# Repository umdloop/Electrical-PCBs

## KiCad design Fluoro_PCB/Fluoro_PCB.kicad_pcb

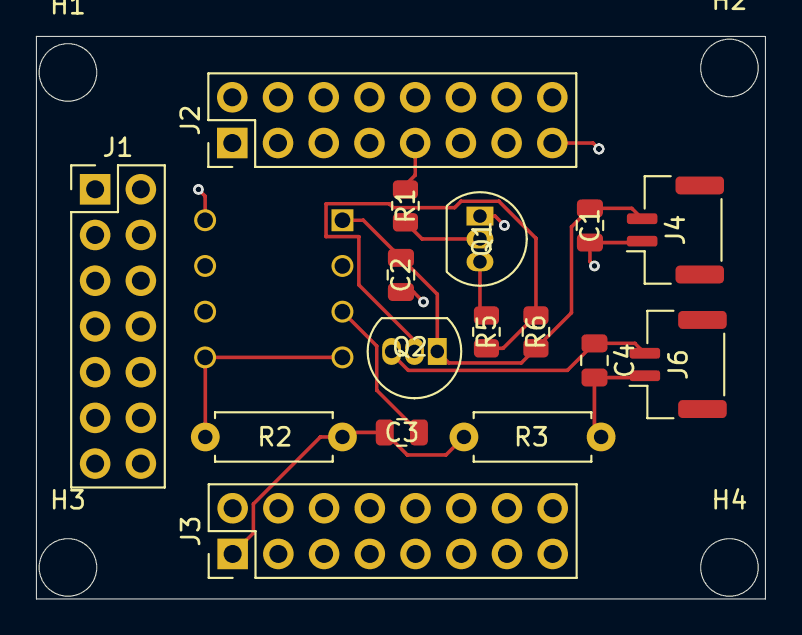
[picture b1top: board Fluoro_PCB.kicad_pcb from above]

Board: 2 copper layers, 40.5 x 31.2 mm, 21 parts (1 on the bottom side), 9 nets.

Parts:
C1, C4: 10uF; C_0805_2012Metric
C2: 100nF; C_0805_2012Metric
C3: 22uF; C_0805_2012Metric
H1, H2, H3, H4: MountingHole; MountingHole_3.2mm_M3_DIN965
J1: Conn_02x07_Odd_Even; PinHeader_2x07_P2.54mm_Vertical
J2, J3: Conn_02x08_Odd_Even; PinHeader_2x08_P2.54mm_Vertical
J4, J6: SM02B-GHS-TB; JST_GH_SM02B-GHS-TB_1x02-1MP_P1.25mm_Horizontal
Q1: S8050; TO-92_Inline
Q2: S8550; TO-92_Inline
R1: 220; R_0805_2012Metric
R2: 18000; R_Axial_DIN0207_L6.3mm_D2.5mm_P7.62mm_Horizontal
R3: 22000; R_Axial_DIN0207_L6.3mm_D2.5mm_P7.62mm_Horizontal
R5: 680; R_0805_2012Metric
R6: 330; R_0805_2012Metric
U1: OPT101P; DIP762W46P254L952H419Q8

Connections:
+5V: C1.1, C2.1, J4.2, Q2.1 (E), R6.1, U1.1 (VS)
/43: C3.1, J3.1, R2.2, R3.2
/54: J2.9, R1.2
GND: C1.2, C2.2, C3.2, C4.2, J2.15, J4.1, J6.1, Q1.1 (E), R3.1, U1.3 (-V), U1.8 (COMMON)
unnamed: Q1.2 (B), R1.1
unnamed: Q1.3 (C), R5.2
unnamed: Q2.2 (B), R5.1, R6.2
unnamed: C4.1, J6.2, Q2.3 (C)
unnamed: R2.1, U1.4 (1MOHM_FB), U1.5 (OUTPUT)

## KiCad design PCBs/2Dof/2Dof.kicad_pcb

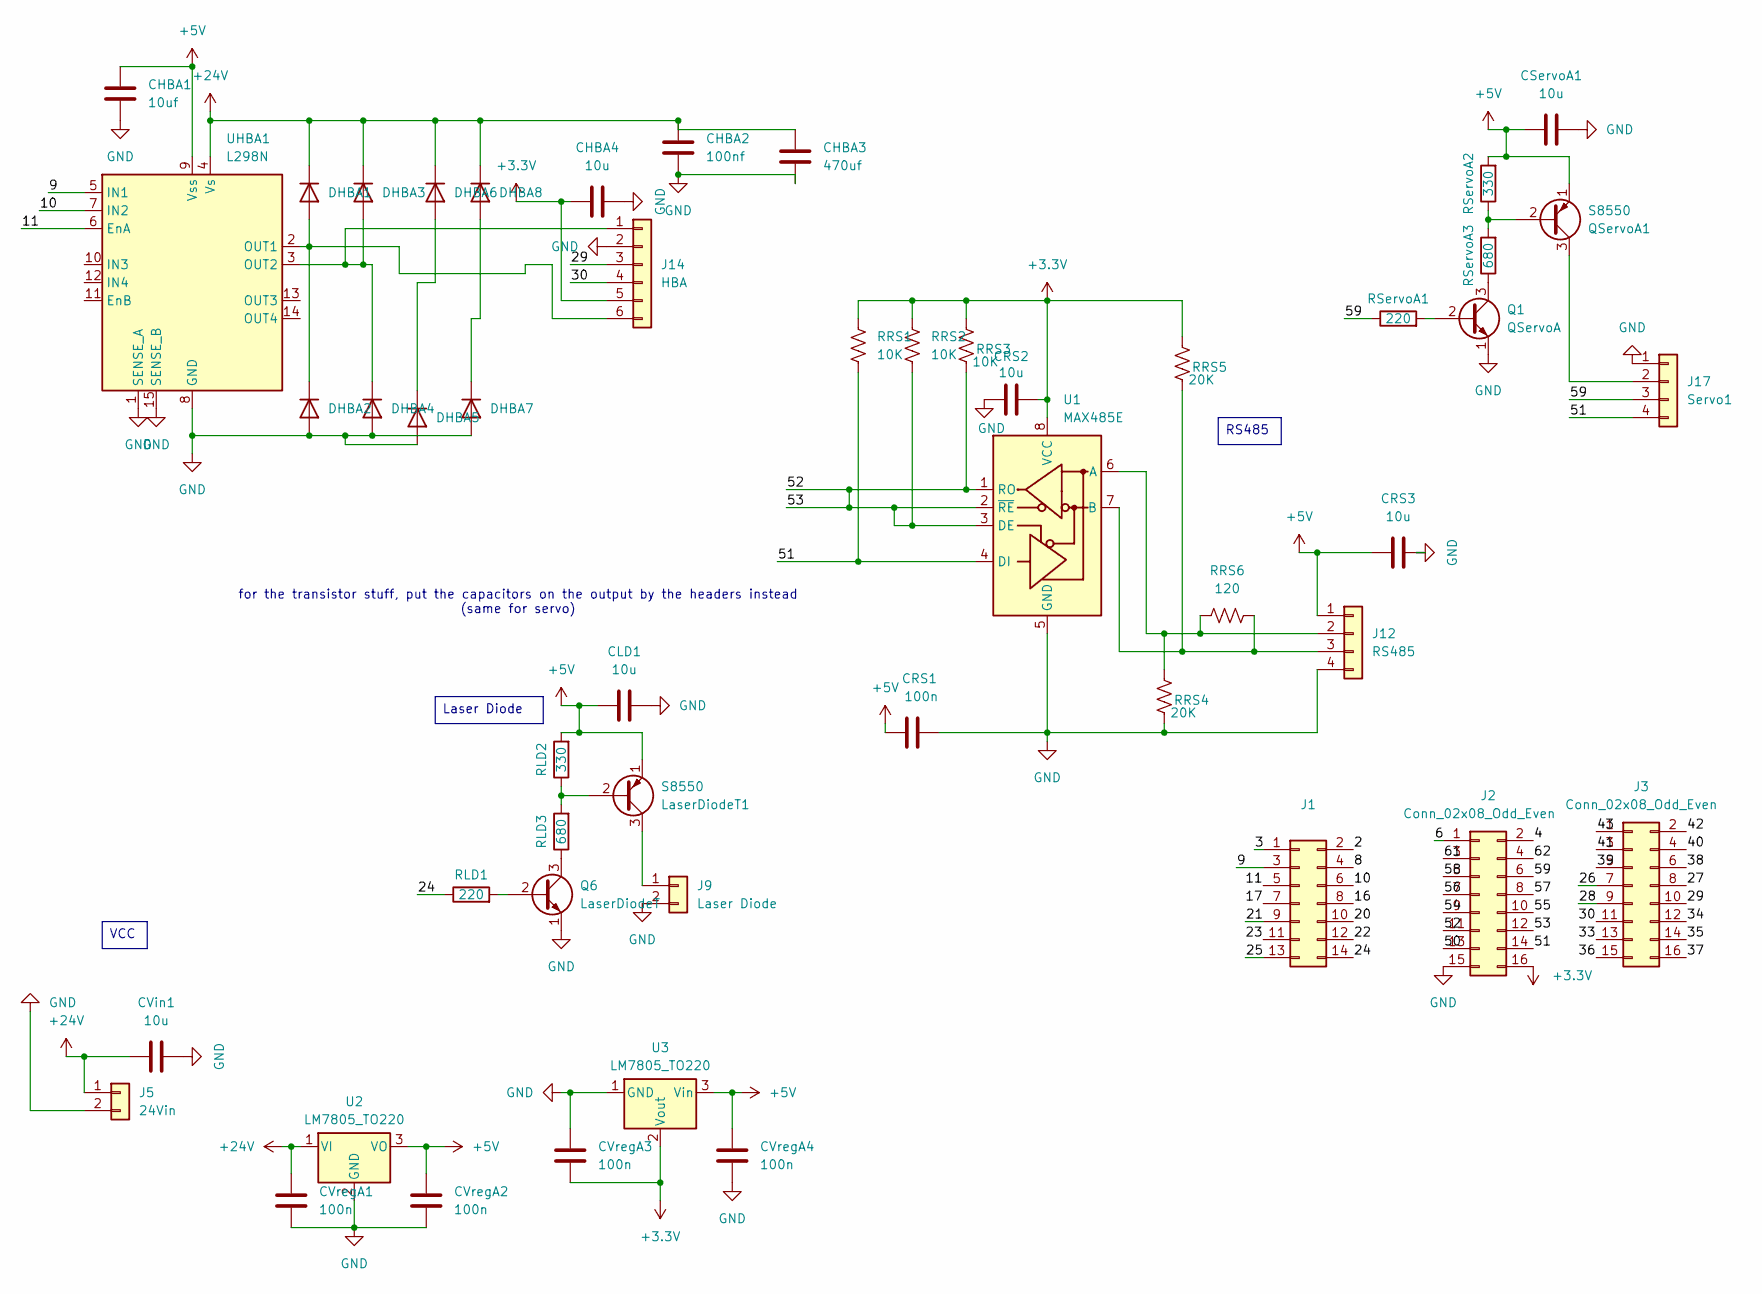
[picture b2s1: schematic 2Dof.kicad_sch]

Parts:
CHBA1: 10uf; C_0805_2012Metric_Pad1.18x1.45mm_HandSolder
CHBA2: 100nf; C_0805_2012Metric_Pad1.18x1.45mm_HandSolder
CHBA3: 470uf; CP_Elec_6.3x7.7
CHBA4: 10u; C_0805_2012Metric_Pad1.18x1.45mm_HandSolder
CLD1: 10u; C_0805_2012Metric_Pad1.18x1.45mm_HandSolder
CRS1: 100n; C_0805_2012Metric_Pad1.18x1.45mm_HandSolder
CRS2, CRS3: 10u; C_0805_2012Metric_Pad1.18x1.45mm_HandSolder
CServoA1: 10u; C_0805_2012Metric_Pad1.18x1.45mm_HandSolder
CVin1: 10u; C_0805_2012Metric_Pad1.18x1.45mm_HandSolder
CVregA1, CVregA2, CVregA3, CVregA4: 100n; C_0805_2012Metric_Pad1.18x1.45mm_HandSolder
DHBA1, DHBA2, DHBA3, DHBA4, DHBA5, DHBA6, DHBA7, DHBA8: 1N4148WT; D_SOD-123
J1: Conn_02x07_Odd_Even; PinHeader_2x07_P2.54mm_Vertical
J2, J3: Conn_02x08_Odd_Even; PinHeader_2x08_P2.54mm_Vertical
J5: 24Vin; Molex_Micro-Fit_3.0_43650-0210_1x02-1MP_P3.00mm_Horizontal
J9: Laser Diode; JST_GH_SM02B-GHS-TB_1x02-1MP_P1.25mm_Horizontal
J12: RS485; JST_GH_SM04B-GHS-TB_1x04-1MP_P1.25mm_Horizontal
J14: HBA; JST_GH_SM06B-GHS-TB_1x06-1MP_P1.25mm_Horizontal
J17: Servo1; JST_GH_SM04B-GHS-TB_1x04-1MP_P1.25mm_Horizontal
LaserDiodeT1: S8550; TO-92_Inline
Q1: QServoA; TO-92_Inline
Q6: LaserDiodeT; TO-92_Inline
QServoA1: S8550; TO-92_Inline
RLD1: 220; R_0402_1005Metric_Pad0.72x0.64mm_HandSolder
RLD2: 330; R_0402_1005Metric_Pad0.72x0.64mm_HandSolder
RLD3: 680; R_0402_1005Metric_Pad0.72x0.64mm_HandSolder
RRS1, RRS2, RRS3: 10K; R_0402_1005Metric_Pad0.72x0.64mm_HandSolder
RRS4, RRS5: 20K; R_0402_1005Metric_Pad0.72x0.64mm_HandSolder
RRS6: 120; R_0402_1005Metric_Pad0.72x0.64mm_HandSolder
RServoA1: 220; R_0402_1005Metric_Pad0.72x0.64mm_HandSolder
RServoA2: 330; R_0402_1005Metric_Pad0.72x0.64mm_HandSolder
RServoA3: 680; R_0402_1005Metric_Pad0.72x0.64mm_HandSolder
U1: MAX485E; SOIC-8_3.9x4.9mm_P1.27mm
U2: LM7805_TO220; TO-220-3_Vertical
U3: LM7805_TO220; SOT-23_Handsoldering
UHBA1: L298N; l298n_with_heatsink

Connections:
+3.3V: CHBA4.1, CRS2.2, CVregA3.1, J2.16, J14.5, RRS1.1, RRS2.1, RRS3.1, RRS5.1, U1.8 (VCC), U3.2 (Vout)
+5V: CHBA1.1, CLD1.2, CRS1.2, CRS3.1, CServoA1.2, CVregA2.2, CVregA4.1, J12.1, LaserDiodeT1.1 (E), QServoA1.1 (E), RLD2.2, RServoA2.2, U2.3 (VO), U3.3 (Vin), UHBA1.9 (Vss)
+24V: CHBA2.1, CHBA3.1, CVin1.1, CVregA1.2, DHBA1.1 (K), DHBA3.1 (K), DHBA6.1 (K), DHBA8.1 (K), J5.1, U2.1 (VI), UHBA1.4 (Vs)
/2: J1.2
/3: J1.1
/4: J2.2
/6: J2.1
/8: J1.4
/9: J1.3, UHBA1.5 (IN1)
/10: J1.6, UHBA1.7 (IN2)
/11: J1.5, UHBA1.6 (EnA)
/16: J1.8
/17: J1.7
/20: J1.10
/21: J1.9
/22: J1.12
/23: J1.11
/24: J1.14, RLD1.1
/25: J1.13
/26: J3.7
/27: J3.8
/28: J3.9
/29: J3.10, J14.3
/30: J3.11, J14.4
/33: J3.13
/34: J3.12
/35: J3.14
/36: J3.15
/37: J3.16
/38: J3.6
/39: J3.5
/40: J3.4
/41: J3.3
/42: J3.2
/43: J3.1
/50: J2.13
/51: J2.14, J17.4, RRS1.2, U1.4 (DI)
/52: J2.11, J2.12, RRS2.2, RRS3.2, U1.1 (RO), U1.2 (~RE), U1.3 (DE)
/54: J2.9
/55: J2.10
/56: J2.7
/57: J2.8
/58: J2.5
/59: J2.6, J17.3, RServoA1.1
/61: J2.3
/62: J2.4
GND: CHBA1.2, CHBA2.2, CHBA3.2, CHBA4.2, CLD1.1, CRS1.1, CRS2.1, CRS3.2, CServoA1.1, CVin1.2, CVregA1.1, CVregA2.1, CVregA3.2, CVregA4.2, DHBA2.2 (A), DHBA4.2 (A), DHBA5.2 (A), DHBA7.2 (A), J2.15, J5.2, J9.2, J12.4, J14.2, J17.1, Q1.1 (E), Q6.1 (E), RRS4.2, U1.5 (GND), U2.2 (GND), U3.1 (GND), UHBA1.1 (SENSE_A), UHBA1.8 (GND), UHBA1.15 (SENSE_B)
unnamed: DHBA1.2 (A), DHBA2.1 (K), J14.6, UHBA1.2 (OUT1)
unnamed: DHBA3.2 (A), DHBA4.1 (K), J14.1, UHBA1.3 (OUT2)
unnamed: DHBA5.1 (K), DHBA6.2 (A)
unnamed: DHBA7.1 (K), DHBA8.2 (A)
unnamed: J9.1, LaserDiodeT1.3 (C)
unnamed: J12.2, RRS4.1, RRS6.1, U1.6 (A)
unnamed: J12.3, RRS5.2, RRS6.2, U1.7 (B)
unnamed: J17.2, QServoA1.3 (C)
unnamed: LaserDiodeT1.2 (B), RLD2.1, RLD3.2
unnamed: Q1.2 (B), RServoA1.2
unnamed: Q1.3 (C), RServoA3.1
unnamed: Q6.2 (B), RLD1.2
unnamed: Q6.3 (C), RLD3.1
unnamed: QServoA1.2 (B), RServoA2.1, RServoA3.2

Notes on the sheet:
for the transistor stuff, put the capacitors on the output by the headers instead (same for servo)
Laser Diode
RS485
VCC

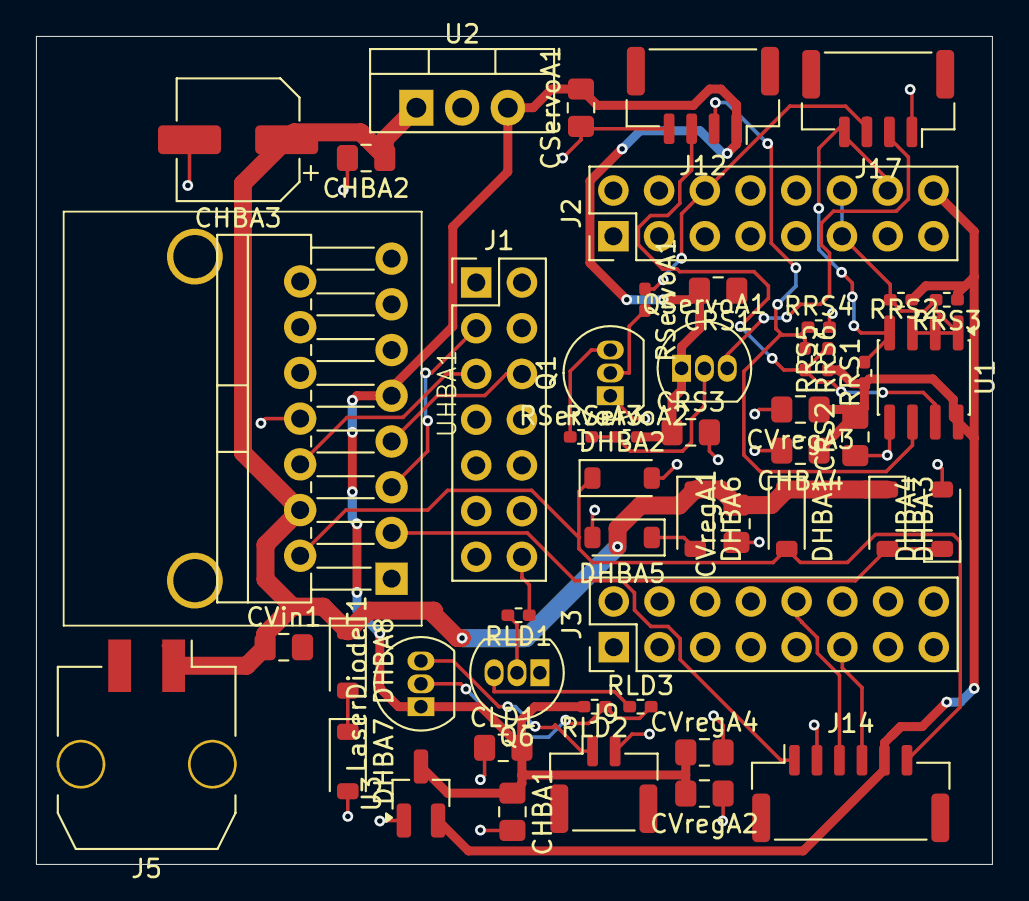
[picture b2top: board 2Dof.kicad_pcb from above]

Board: 2 copper layers, 53.1 x 46.0 mm, 50 parts (0 on the bottom side), 27 nets.

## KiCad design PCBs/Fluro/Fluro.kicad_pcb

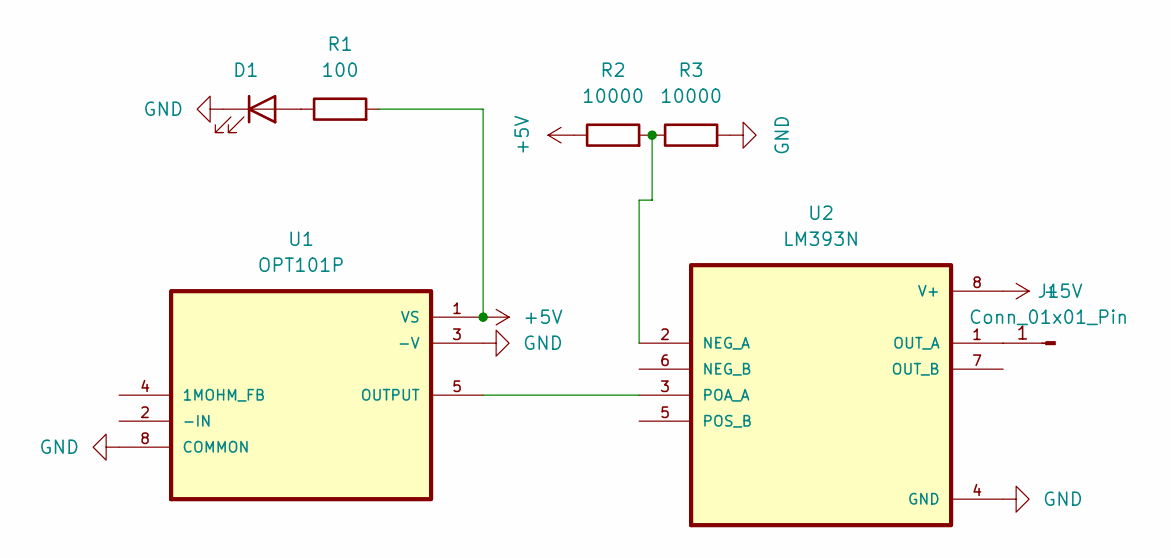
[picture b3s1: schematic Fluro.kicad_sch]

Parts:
D1: LED; LED_D3.0mm_Horizontal_O3.81mm_Z6.0mm
J1: Conn_01x01_Pin; FanPinHeader_1x03_P2.54mm_Vertical
R1: 100; R_0201_0603Metric
R2, R3: 10000; R_0201_0603Metric
U1: OPT101P; DIP762W46P254L952H419Q8
U2: LM393N; DIP794W45P254L959H508Q8

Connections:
+5V: R1.2, R2.1, U1.1 (VS), U2.8 (V+)
GND: D1.1 (K), R3.2, U1.3 (-V), U1.8 (COMMON), U2.4 (GND)
unnamed: D1.2 (A), R1.1
unnamed: J1.1, U2.1 (OUT_A)
unnamed: U1.5 (OUTPUT), U2.3 (POA_A)
unnamed: R2.2, R3.1, U2.2 (NEG_A)

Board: 2 copper layers, 7 parts (0 on the bottom side), 6 nets, no tracks yet.

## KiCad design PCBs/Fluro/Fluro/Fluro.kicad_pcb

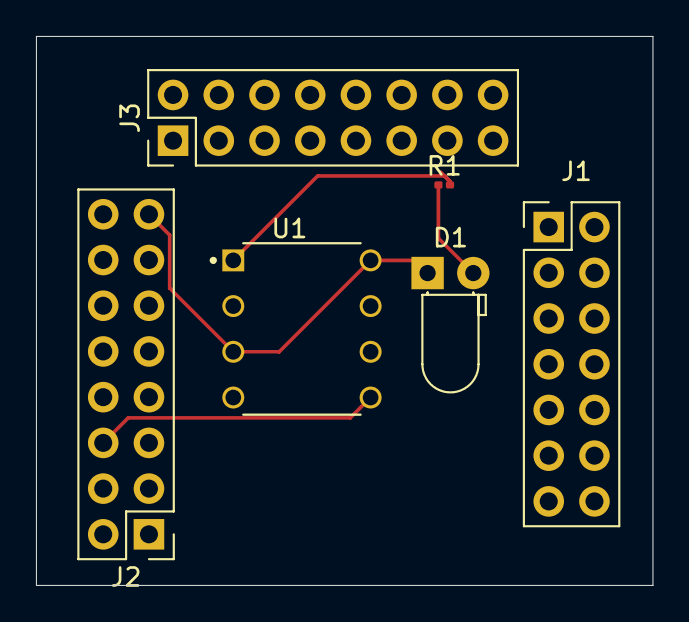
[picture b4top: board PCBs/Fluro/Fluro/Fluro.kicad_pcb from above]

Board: 2 copper layers, 34.2 x 30.5 mm, 6 parts (0 on the bottom side), 4 nets.

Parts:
D1: LED; LED_D3.0mm_Horizontal_O1.27mm_Z2.0mm_Clear
J1: Conn_02x07_Odd_Even; PinHeader_2x07_P2.54mm_Vertical
J2, J3: Conn_02x08_Odd_Even; PinHeader_2x08_P2.54mm_Vertical
R1: 100; R_0201_0603Metric
U1: OPT101P; DIP762W46P254L952H419Q8

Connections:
+5V: R1.2, U1.1 (VS)
/59: J2.6, U1.5 (OUTPUT)
GND: D1.1 (K), J2.15, U1.3 (-V), U1.8 (COMMON)
unnamed: D1.2 (A), R1.1
